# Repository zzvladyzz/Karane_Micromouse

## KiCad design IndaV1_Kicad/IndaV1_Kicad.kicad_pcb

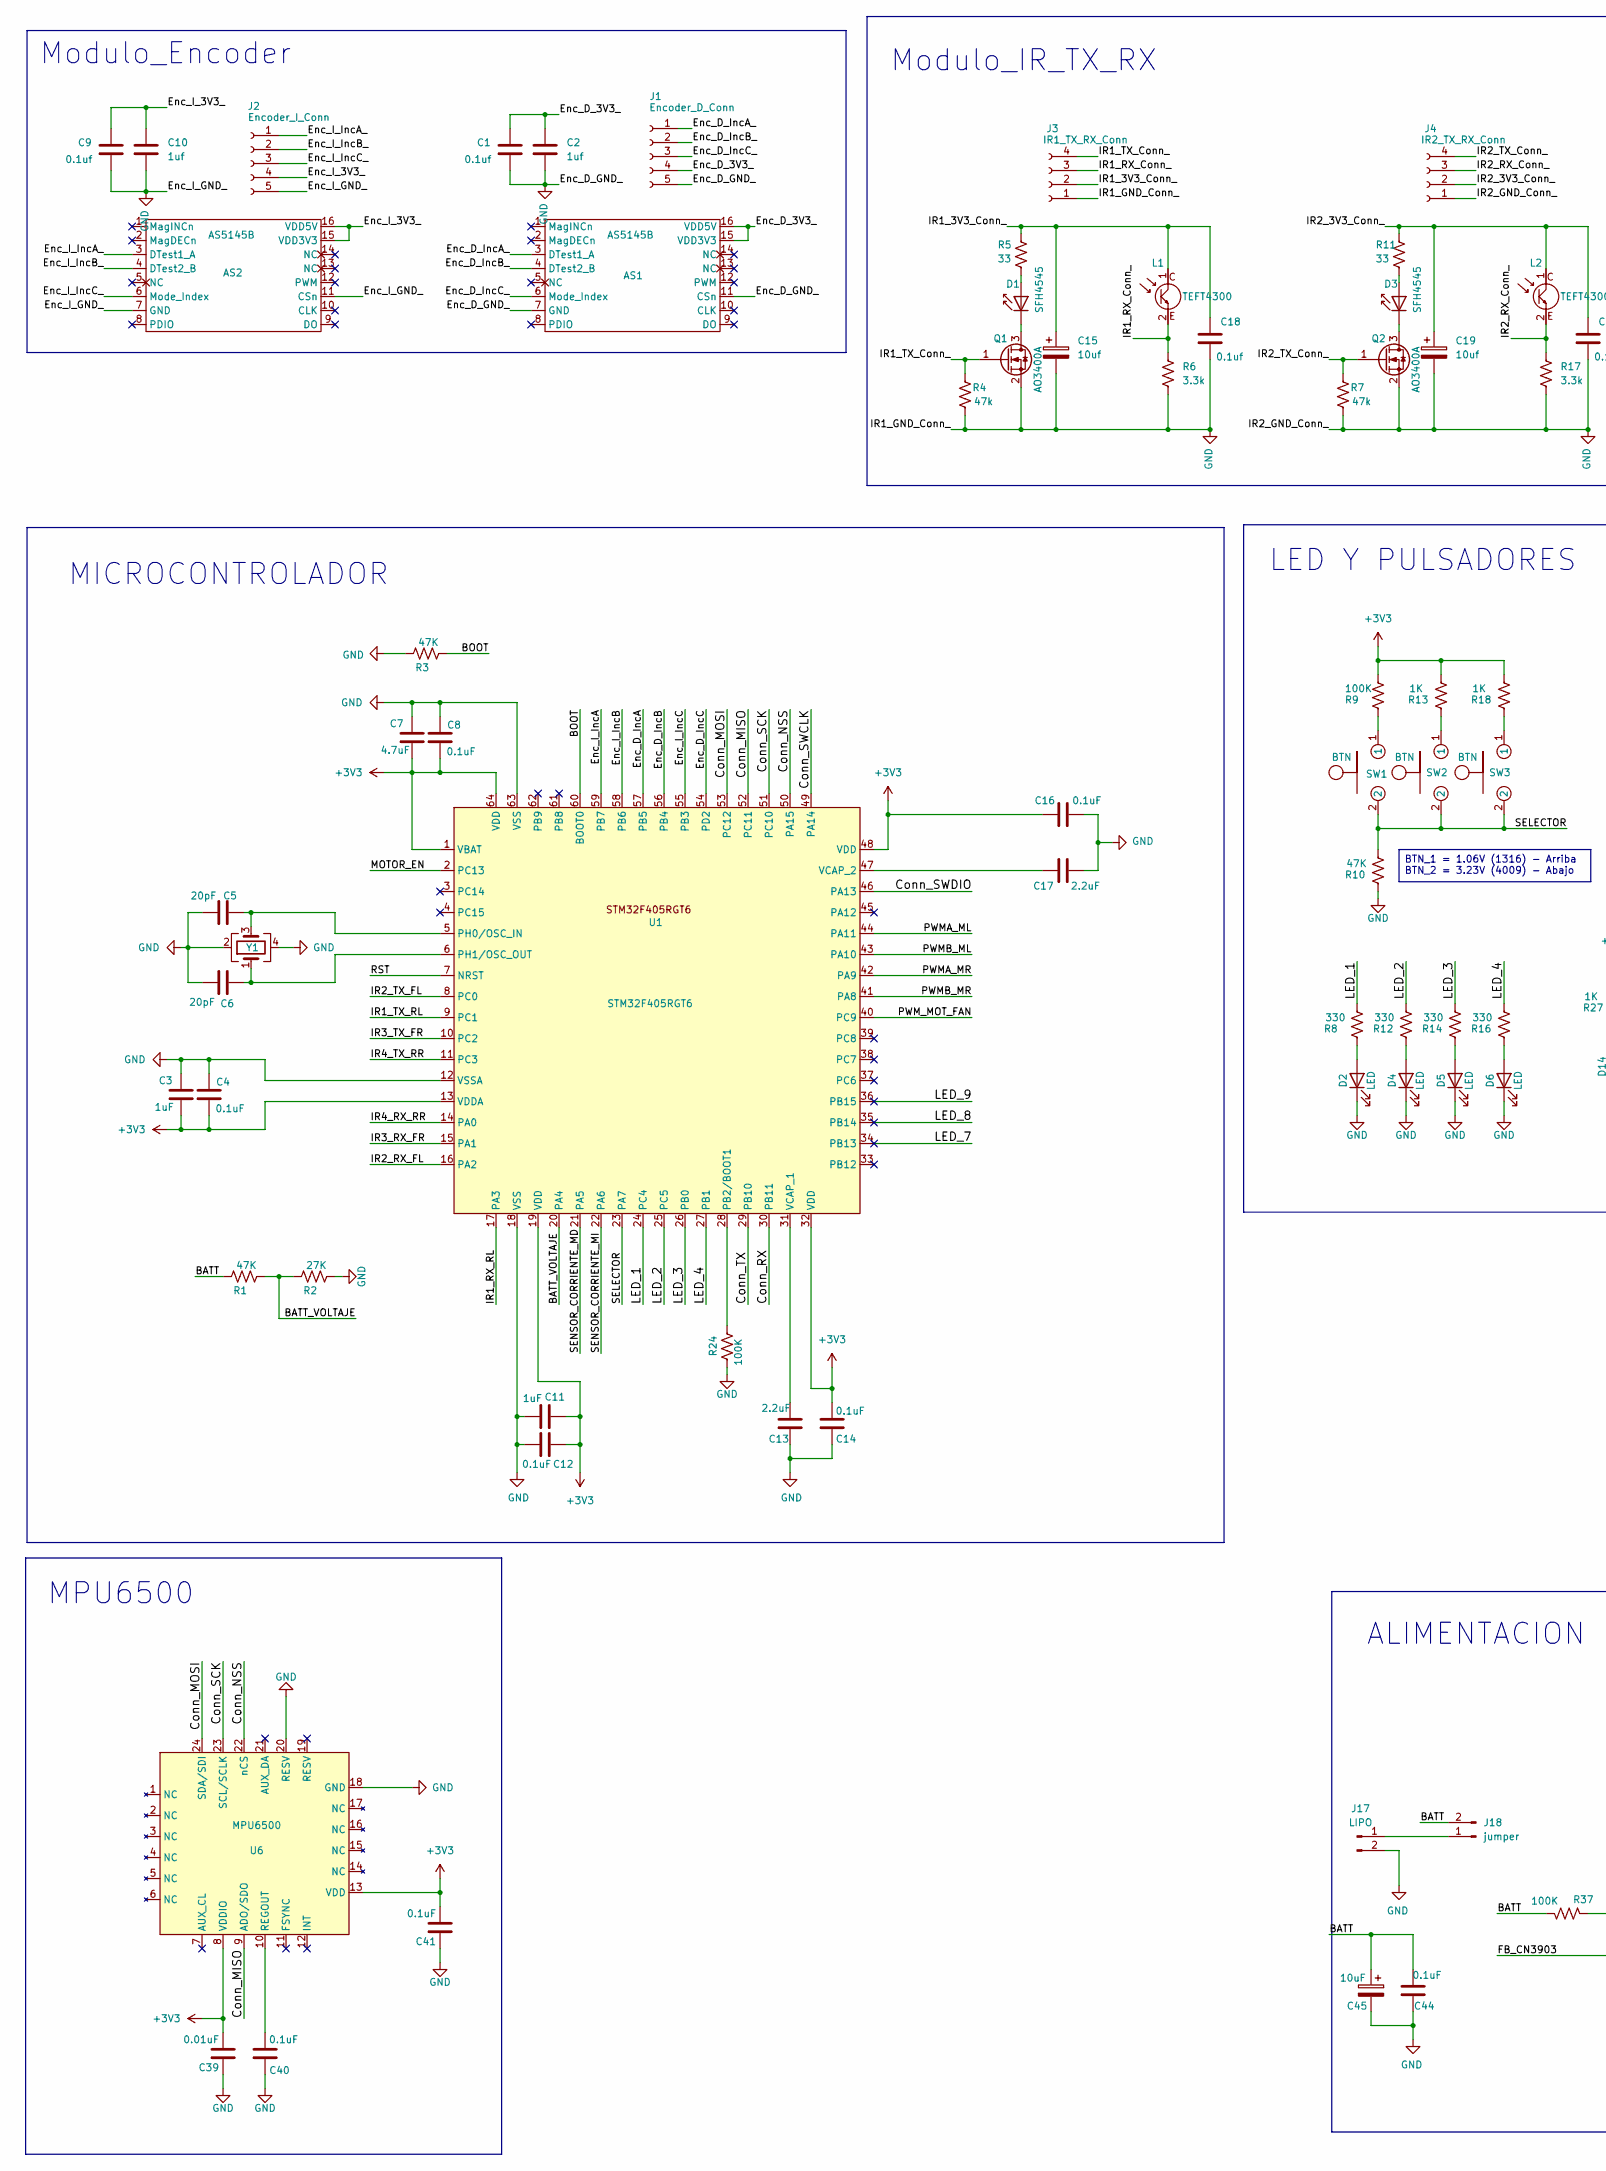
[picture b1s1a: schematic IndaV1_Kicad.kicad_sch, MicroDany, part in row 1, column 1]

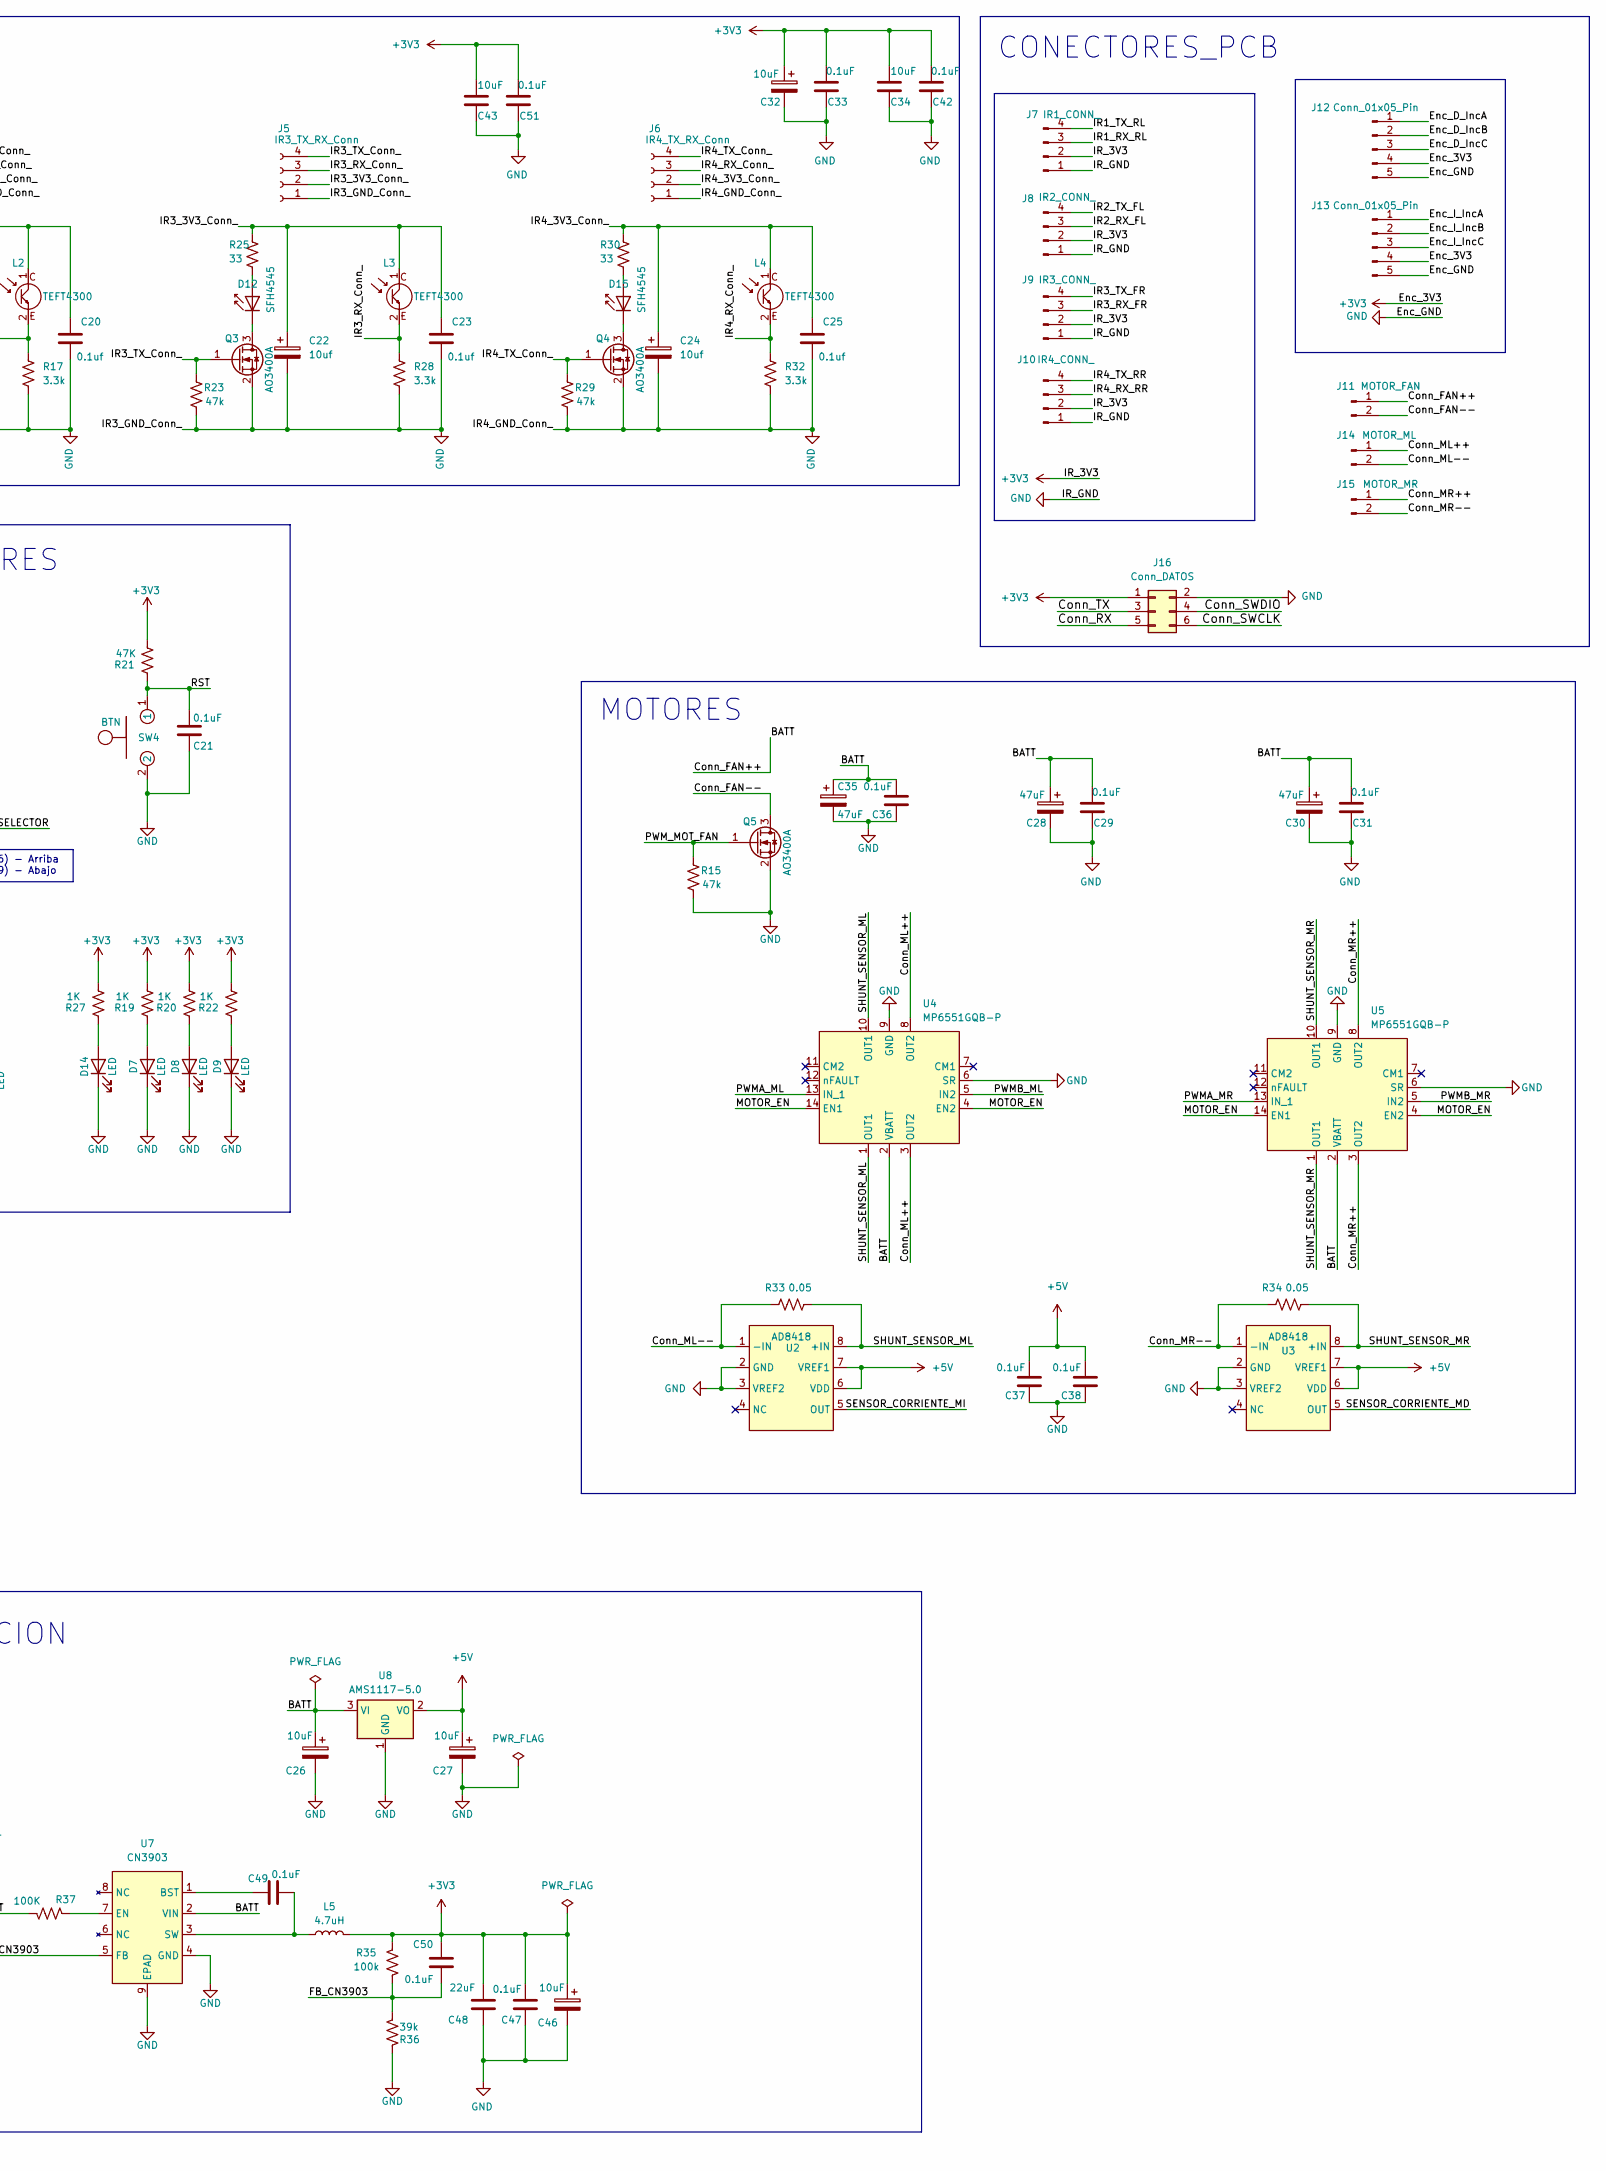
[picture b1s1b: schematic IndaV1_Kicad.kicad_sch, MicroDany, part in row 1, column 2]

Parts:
AS1, AS2: AS5145B; SSOP-16_5.3x6.2mm_P0.65mm
C1, C9, C18, C20, C23, C25: 0.1uf; C_0603_1608Metric_Pad1.08x0.95mm_HandSolder
C2, C10: 1uf; C_1206_3216Metric_Pad1.33x1.80mm_HandSolder
C3, C11: 1uF; C_0603_1608Metric_Pad1.08x0.95mm_HandSolder
C4, C8, C12, C14, C16, C21, C29, C31, C36, C37, C38, C40, C41, C47, C49, C50: 0.1uF; C_0603_1608Metric_Pad1.08x0.95mm_HandSolder
C5, C6: 20pF; C_0603_1608Metric_Pad1.08x0.95mm_HandSolder
C7: 4.7uF; C_0603_1608Metric_Pad1.08x0.95mm_HandSolder
C13, C17: 2.2uF; C_0603_1608Metric_Pad1.08x0.95mm_HandSolder
C15, C19, C22, C24: 10uf; C_0603_1608Metric_Pad1.08x0.95mm_HandSolder
C26, C27, C34, C43: 10uF; C_1206_3216Metric_Pad1.33x1.80mm_HandSolder
C28, C30, C35: 47uF; CP_EIA-7343-15_Kemet-W_HandSolder
C32, C45: 10uF; CP_EIA-7343-15_Kemet-W_HandSolder
C33, C42, C44, C51: 0.1uF; C_1206_3216Metric_Pad1.33x1.80mm_HandSolder
C39: 0.01uF; C_0603_1608Metric_Pad1.08x0.95mm_HandSolder
C46: 10uF; CP_EIA-6032-15_Kemet-U_HandSolder
C48: 22uF; C_0603_1608Metric_Pad1.08x0.95mm_HandSolder
D1, D3, D12, D15: SFH4545; SFH4545_LED
D2, D4, D5, D6, D7, D8, D9, D14: LED; LED_1206_3216Metric_Pad1.42x1.75mm_HandSolder
J1: Encoder_D_Conn; AS5145_Mod
J2: Encoder_I_Conn; AS5145_Mod
J3: IR1_TX_RX_Conn; SFH_TEFT_Mod
J4: IR2_TX_RX_Conn; SFH_TEFT_Mod
J5: IR3_TX_RX_Conn; SFH_TEFT_Mod
J6: IR4_TX_RX_Conn; SFH_TEFT_Mod
J7: IR1_CONN_; SFH_TEFT_CONN_PCB
J8: IR2_CONN_; SFH_TEFT_CONN_PCB
J9: IR3_CONN_; SFH_TEFT_CONN_PCB
J10: IR4_CONN_; SFH_TEFT_CONN_PCB
J11: MOTOR_FAN; PinHeader_1x02_P2.54mm_Vertical
J12, J13: Conn_01x05_Pin; AS5145_CONN_PCB
J14: MOTOR_ML; PinHeader_1x02_P2.54mm_Vertical
J15: MOTOR_MR; PinHeader_1x02_P2.54mm_Vertical
J16: Conn_DATOS; PinHeader_2x03_P2.54mm_Vertical
J17: LIPO; PinHeader_1x02_P2.54mm_Vertical
J18: jumper; PinHeader_1x02_P2.54mm_Vertical
L1, L2, L3, L4: TEFT4300; TEFT4300_LED
L5: 4.7uH; L_Wuerth_HCM-7050
Q1, Q2, Q3, Q4, Q5: AO3400A; SOT-23
R1, R3, R10, R21: 47K; R_0805_2012Metric_Pad1.20x1.40mm_HandSolder
R2: 27K; R_0805_2012Metric_Pad1.20x1.40mm_HandSolder
R4, R7, R15, R23, R29: 47k; R_0805_2012Metric_Pad1.20x1.40mm_HandSolder
R5, R11, R25, R30: 33; R_0805_2012Metric_Pad1.20x1.40mm_HandSolder
R6, R17, R28, R32: 3.3k; R_0805_2012Metric_Pad1.20x1.40mm_HandSolder
R8, R12, R14, R16: 330; R_0805_2012Metric_Pad1.20x1.40mm_HandSolder
R9, R24, R37: 100K; R_0805_2012Metric_Pad1.20x1.40mm_HandSolder
R13, R18, R19, R20, R22, R27: 1K; R_0805_2012Metric_Pad1.20x1.40mm_HandSolder
R33, R34: 0.05; R_2512_6332Metric_Pad1.40x3.35mm_HandSolder
R35: 100k; R_0805_2012Metric_Pad1.20x1.40mm_HandSolder
R36: 39k; R_0805_2012Metric_Pad1.20x1.40mm_HandSolder
SW1, SW2, SW3, SW4: BTN; SW_Push_SPST_NO_Alps_SKRK
U1: STM32F405RGT6; LQFP-64_10x10mm_P0.5mm
U2, U3: AD8418
U4, U5: MP6551GQB-P; MP6551
U6: MPU6500; InvenSense_QFN-24_3x3mm_P0.4mm
U7: CN3903; SOP-8-1EP_4.57x4.57mm_P1.27mm_EP4.57x4.45mm
U8: AMS1117-5.0; SOT-223-3_TabPin2
Y1: Crystal_GND24; Crystal_SMD_TXC_7M-4Pin_3.2x2.5mm_HandSoldering

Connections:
+3V3: C3.1, C4.2, C7.1, C8.2, C11.2, C12.1, C14.1, C16.1, C32.1, C33.1, C34.1, C39.2, C41.2, C42.1, C43.1, C46.1, C47.1, C48.1, C50.2, C51.1, J7.2, J8.2, J9.2, J10.2, J12.4, J13.4, J16.1, L5.1, R9.1, R13.1, R18.1, R19.1, R20.1, R21.1, R22.1, R27.1, R35.1, U1.1 (VBAT), U1.13 (VDDA), U1.19 (VDD), U1.32 (VDD), U1.48 (VDD), U1.64 (VDD), U6.8 (VDDIO), U6.13 (VDD)
+5V: C27.1, C37.2, C38.2, U2.6 (VDD), U2.7 (VREF1), U3.6 (VDD), U3.7 (VREF1), U8.2 (VO)
/BATT: C26.1, C28.1, C29.1, C30.1, C31.1, C35.1, C36.2, C44.1, C45.1, J11.1, J18.2, R1.2, R37.2, U4.2 (VBATT), U5.2 (VBATT), U7.2 (VIN), U8.3 (VI)
/BATT_VOLTAJE: R1.1, R2.2, U1.20 (PA4)
/BOOT: R3.1, U1.60 (BOOT0)
/Conn_FAN--: J11.2, Q5.3 (D)
/Conn_MISO: U1.52 (PC11), U6.9 (ADO/SDO)
/Conn_ML++: J14.1, U4.3 (OUT2), U4.8 (OUT2)
/Conn_ML--: J14.2, R33.1, U2.1 (-IN)
/Conn_MOSI: U1.53 (PC12), U6.24 (SDA/SDI)
/Conn_MR++: J15.1, U5.3 (OUT2), U5.8 (OUT2)
/Conn_MR--: J15.2, R34.1, U3.1 (-IN)
/Conn_NSS: U1.50 (PA15), U6.22 (nCS)
/Conn_RX: J16.5, U1.30 (PB11)
/Conn_SCK: U1.51 (PC10), U6.23 (SCL/SCLK)
/Conn_SWCLK: J16.6, U1.49 (PA14)
/Conn_SWDIO: J16.4, U1.46 (PA13)
/Conn_TX: J16.3, U1.29 (PB10)
/Enc_D_3V3_: AS1.15 (VDD3V3), AS1.16 (VDD5V), C1.1, C2.1, J1.4
/Enc_D_IncA: J12.1, U1.57 (PB5)
/Enc_D_IncA_: AS1.3 (DTest1_A), J1.1
/Enc_D_IncB: J12.2, U1.56 (PB4)
/Enc_D_IncB_: AS1.4 (DTest2_B), J1.2
/Enc_D_IncC: J12.3, U1.54 (PD2)
/Enc_D_IncC_: AS1.6 (Mode_Index), J1.3
/Enc_I_3V3_: AS2.15 (VDD3V3), AS2.16 (VDD5V), C9.1, C10.1, J2.4
/Enc_I_IncA: J13.1, U1.59 (PB7)
/Enc_I_IncA_: AS2.3 (DTest1_A), J2.1
/Enc_I_IncB: J13.2, U1.58 (PB6)
/Enc_I_IncB_: AS2.4 (DTest2_B), J2.2
/Enc_I_IncC: J13.3, U1.55 (PB3)
/Enc_I_IncC_: AS2.6 (Mode_Index), J2.3
/FB_CN3903: C50.1, R35.2, R36.1, U7.5 (FB)
/IR1_3V3_Conn_: C15.1, C18.1, J3.2, L1.1 (C), R5.1
/IR1_RX_Conn_: J3.3, L1.2 (E), R6.1
/IR1_RX_RL: J7.3, U1.17 (PA3)
/IR1_TX_Conn_: J3.4, Q1.1 (G), R4.1
/IR1_TX_RL: J7.4, U1.9 (PC1)
/IR2_3V3_Conn_: C19.1, C20.1, J4.2, L2.1 (C), R11.1
/IR2_RX_Conn_: J4.3, L2.2 (E), R17.1
/IR2_RX_FL: J8.3, U1.16 (PA2)
/IR2_TX_Conn_: J4.4, Q2.1 (G), R7.1
/IR2_TX_FL: J8.4, U1.8 (PC0)
/IR3_3V3_Conn_: C22.1, C23.1, J5.2, L3.1 (C), R25.1
/IR3_RX_Conn_: J5.3, L3.2 (E), R28.1
/IR3_RX_FR: J9.3, U1.15 (PA1)
/IR3_TX_Conn_: J5.4, Q3.1 (G), R23.1
/IR3_TX_FR: J9.4, U1.10 (PC2)
/IR4_3V3_Conn_: C24.1, C25.1, J6.2, L4.1 (C), R30.1
/IR4_RX_Conn_: J6.3, L4.2 (E), R32.1
/IR4_RX_RR: J10.3, U1.14 (PA0)
/IR4_TX_Conn_: J6.4, Q4.1 (G), R29.1
/IR4_TX_RR: J10.4, U1.11 (PC3)
/LED_1: R8.1, U1.24 (PC4)
/LED_2: R12.1, U1.25 (PC5)
/LED_3: R14.1, U1.26 (PB0)
/LED_4: R16.1, U1.27 (PB1)
/LED_7: U1.34 (PB13)
/LED_8: U1.35 (PB14)
/LED_9: U1.36 (PB15)
/MOTOR_EN: U1.2 (PC13), U4.4 (EN2), U4.14 (EN1), U5.4 (EN2), U5.14 (EN1)
/PWMA_ML: U1.44 (PA11), U4.13 (IN_1)
/PWMA_MR: U1.42 (PA9), U5.13 (IN_1)
/PWMB_ML: U1.43 (PA10), U4.5 (IN2)
/PWMB_MR: U1.41 (PA8), U5.5 (IN2)
/PWM_MOT_FAN: Q5.1 (G), R15.1, U1.40 (PC9)
/RST: C21.1, R21.2, SW4.1, U1.7 (NRST)
/SELECTOR: R10.1, SW1.2, SW2.2, SW3.2, U1.23 (PA7)
/SENSOR_CORRIENTE_MD: U1.21 (PA5), U3.5 (OUT)
/SENSOR_CORRIENTE_MI: U1.22 (PA6), U2.5 (OUT)
/SHUNT_SENSOR_ML: R33.2, U2.8 (+IN), U4.1 (OUT1), U4.10 (OUT1)
/SHUNT_SENSOR_MR: R34.2, U3.8 (+IN), U5.1 (OUT1), U5.10 (OUT1)
GND: AS1.7 (GND), AS1.11 (CSn), AS2.7 (GND), AS2.11 (CSn), C1.2, C2.2, C3.2, C4.1, C5.1, C6.1, C7.2, C8.1, C9.2, C10.2, C11.1, C12.2, C13.2, C14.2, C15.2, C16.2, C17.1, C18.2, C19.2, C20.2, C21.2, C22.2, C23.2, C24.2, C25.2, C26.2, C27.2, C28.2, C29.2, C30.2, C31.2, C32.2, C33.2, C34.2, C35.2, C36.1, C37.1, C38.1, C39.1, C40.1, C41.1, C42.2, C43.2, C44.2, C45.2, C46.2, C47.2, C48.2, C51.2, D2.1 (K), D4.1 (K), D5.1 (K), D6.1 (K), D7.1 (K), D8.1 (K), D9.1 (K), D14.1 (K), J1.5, J2.5, J3.1, J4.1, J5.1, J6.1, J7.1, J8.1, J9.1, J10.1, J12.5, J13.5, J16.2, J17.2, Q1.2 (S), Q2.2 (S), Q3.2 (S), Q4.2 (S), Q5.2 (S), R2.1, R3.2, R4.2, R6.2, R7.2, R10.2, R15.2, R17.2, R23.2, R24.1, R28.2, R29.2, R32.2, R36.2, SW4.2, U1.12 (VSSA), U1.18 (VSS), U1.63 (VSS), U2.2 (GND), U2.3 (VREF2), U3.2 (GND), U3.3 (VREF2), U4.6 (SR), U4.9 (GND), U5.6 (SR), U5.9 (GND), U6.18 (GND), U6.20 (RESV), U7.4 (GND), U7.9 (EPAD), U8.1 (GND), Y1.2, Y1.4
unnamed: D1.2 (A), R5.2
unnamed: D1.1 (K), Q1.3 (D)
unnamed: D2.2 (A), R8.2
unnamed: D3.2 (A), R11.2
unnamed: D3.1 (K), Q2.3 (D)
unnamed: D4.2 (A), R12.2
unnamed: D5.2 (A), R14.2
unnamed: D6.2 (A), R16.2
unnamed: D7.2 (A), R19.2
unnamed: D8.2 (A), R20.2
unnamed: D9.2 (A), R22.2
unnamed: D12.2 (A), R25.2
unnamed: D12.1 (K), Q3.3 (D)
unnamed: D14.2 (A), R27.2
unnamed: D15.2 (A), R30.2
unnamed: D15.1 (K), Q4.3 (D)
unnamed: J17.1, J18.1
unnamed: R9.2, SW1.1
unnamed: R13.2, SW2.1
unnamed: R18.2, SW3.1
unnamed: R24.2, U1.28 (PB2/BOOT1)
unnamed: C5.2, U1.5 (PH0/OSC_IN), Y1.3
unnamed: C6.2, U1.6 (PH1/OSC_OUT), Y1.1
unnamed: C13.1, U1.31 (VCAP_1)
unnamed: C17.2, U1.47 (VCAP_2)
unnamed: C40.2, U6.10 (REGOUT)
unnamed: C49.2, U7.1 (BST)
unnamed: R37.1, U7.7 (EN)
unnamed: C49.1, L5.2, U7.3 (SW)

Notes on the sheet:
CONECTORES_PCB
MPU6500
MOTORES
Modulo_IR_TX_RX
ALIMENTACION
LED Y PULSADORES
Modulo_Encoder
MICROCONTROLADOR
BTN_1 = 1.06V (1316) - Arriba BTN_2 = 3.23V (4009) - Abajo

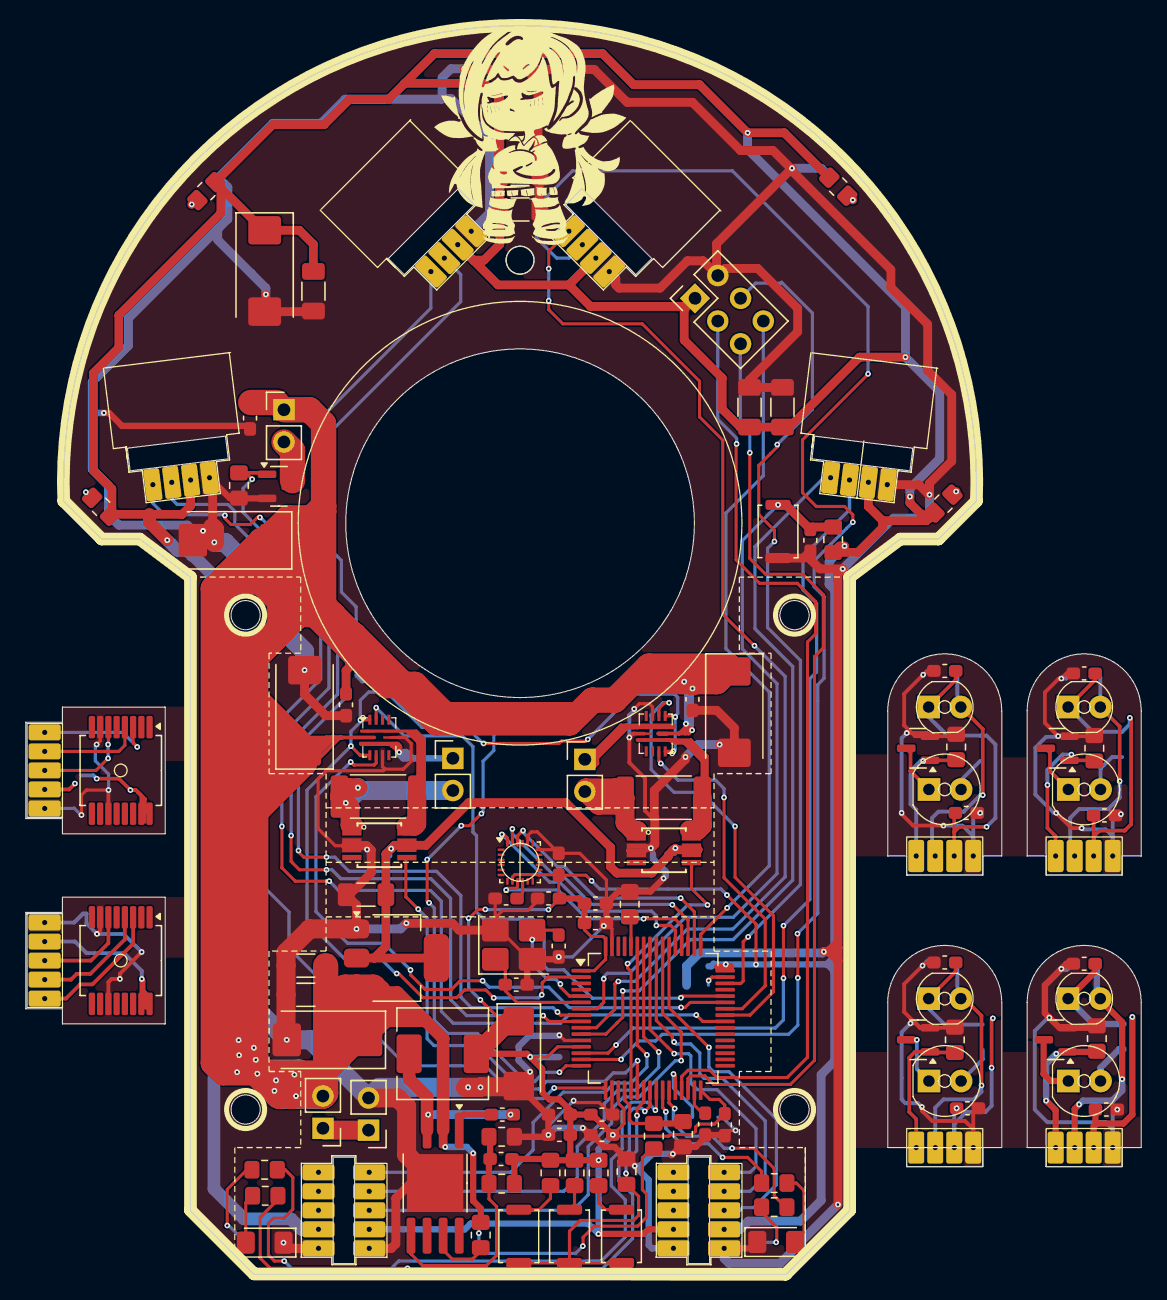
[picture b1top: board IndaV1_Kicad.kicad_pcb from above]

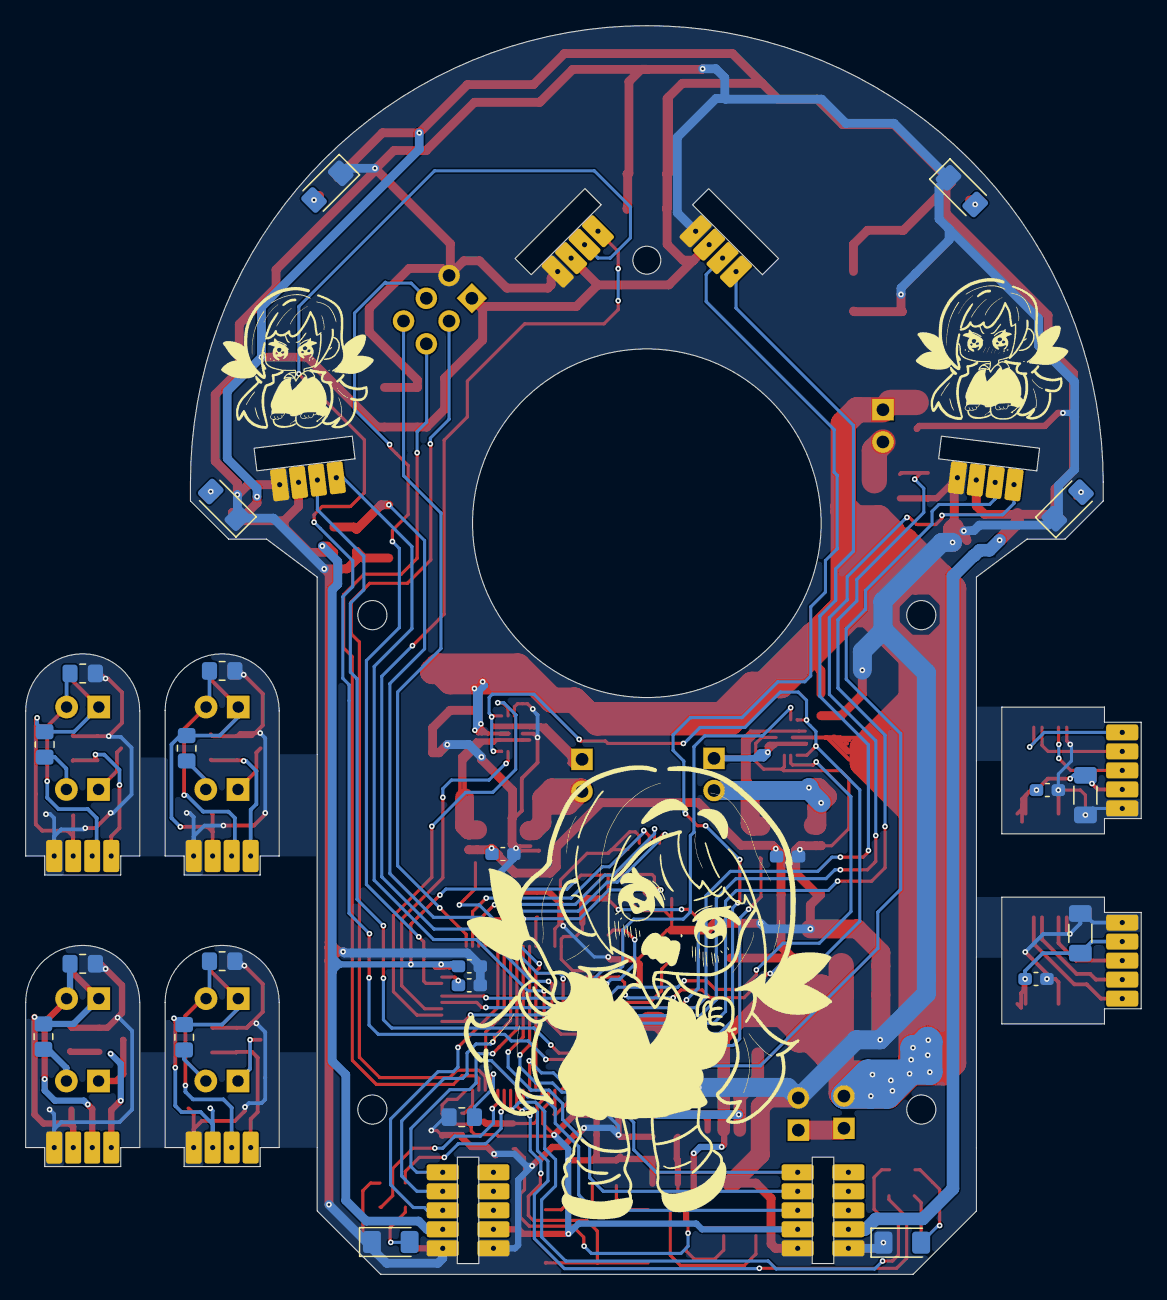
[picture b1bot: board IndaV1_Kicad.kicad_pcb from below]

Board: 2 copper layers, 72.0 x 98.5 mm, 145 parts (28 on the bottom side), 99 nets.

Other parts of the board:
., .#2, .#3, .#4: LOGO
